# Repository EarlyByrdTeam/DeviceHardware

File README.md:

# DeviceHardware
EAGLE CAD files for EB device

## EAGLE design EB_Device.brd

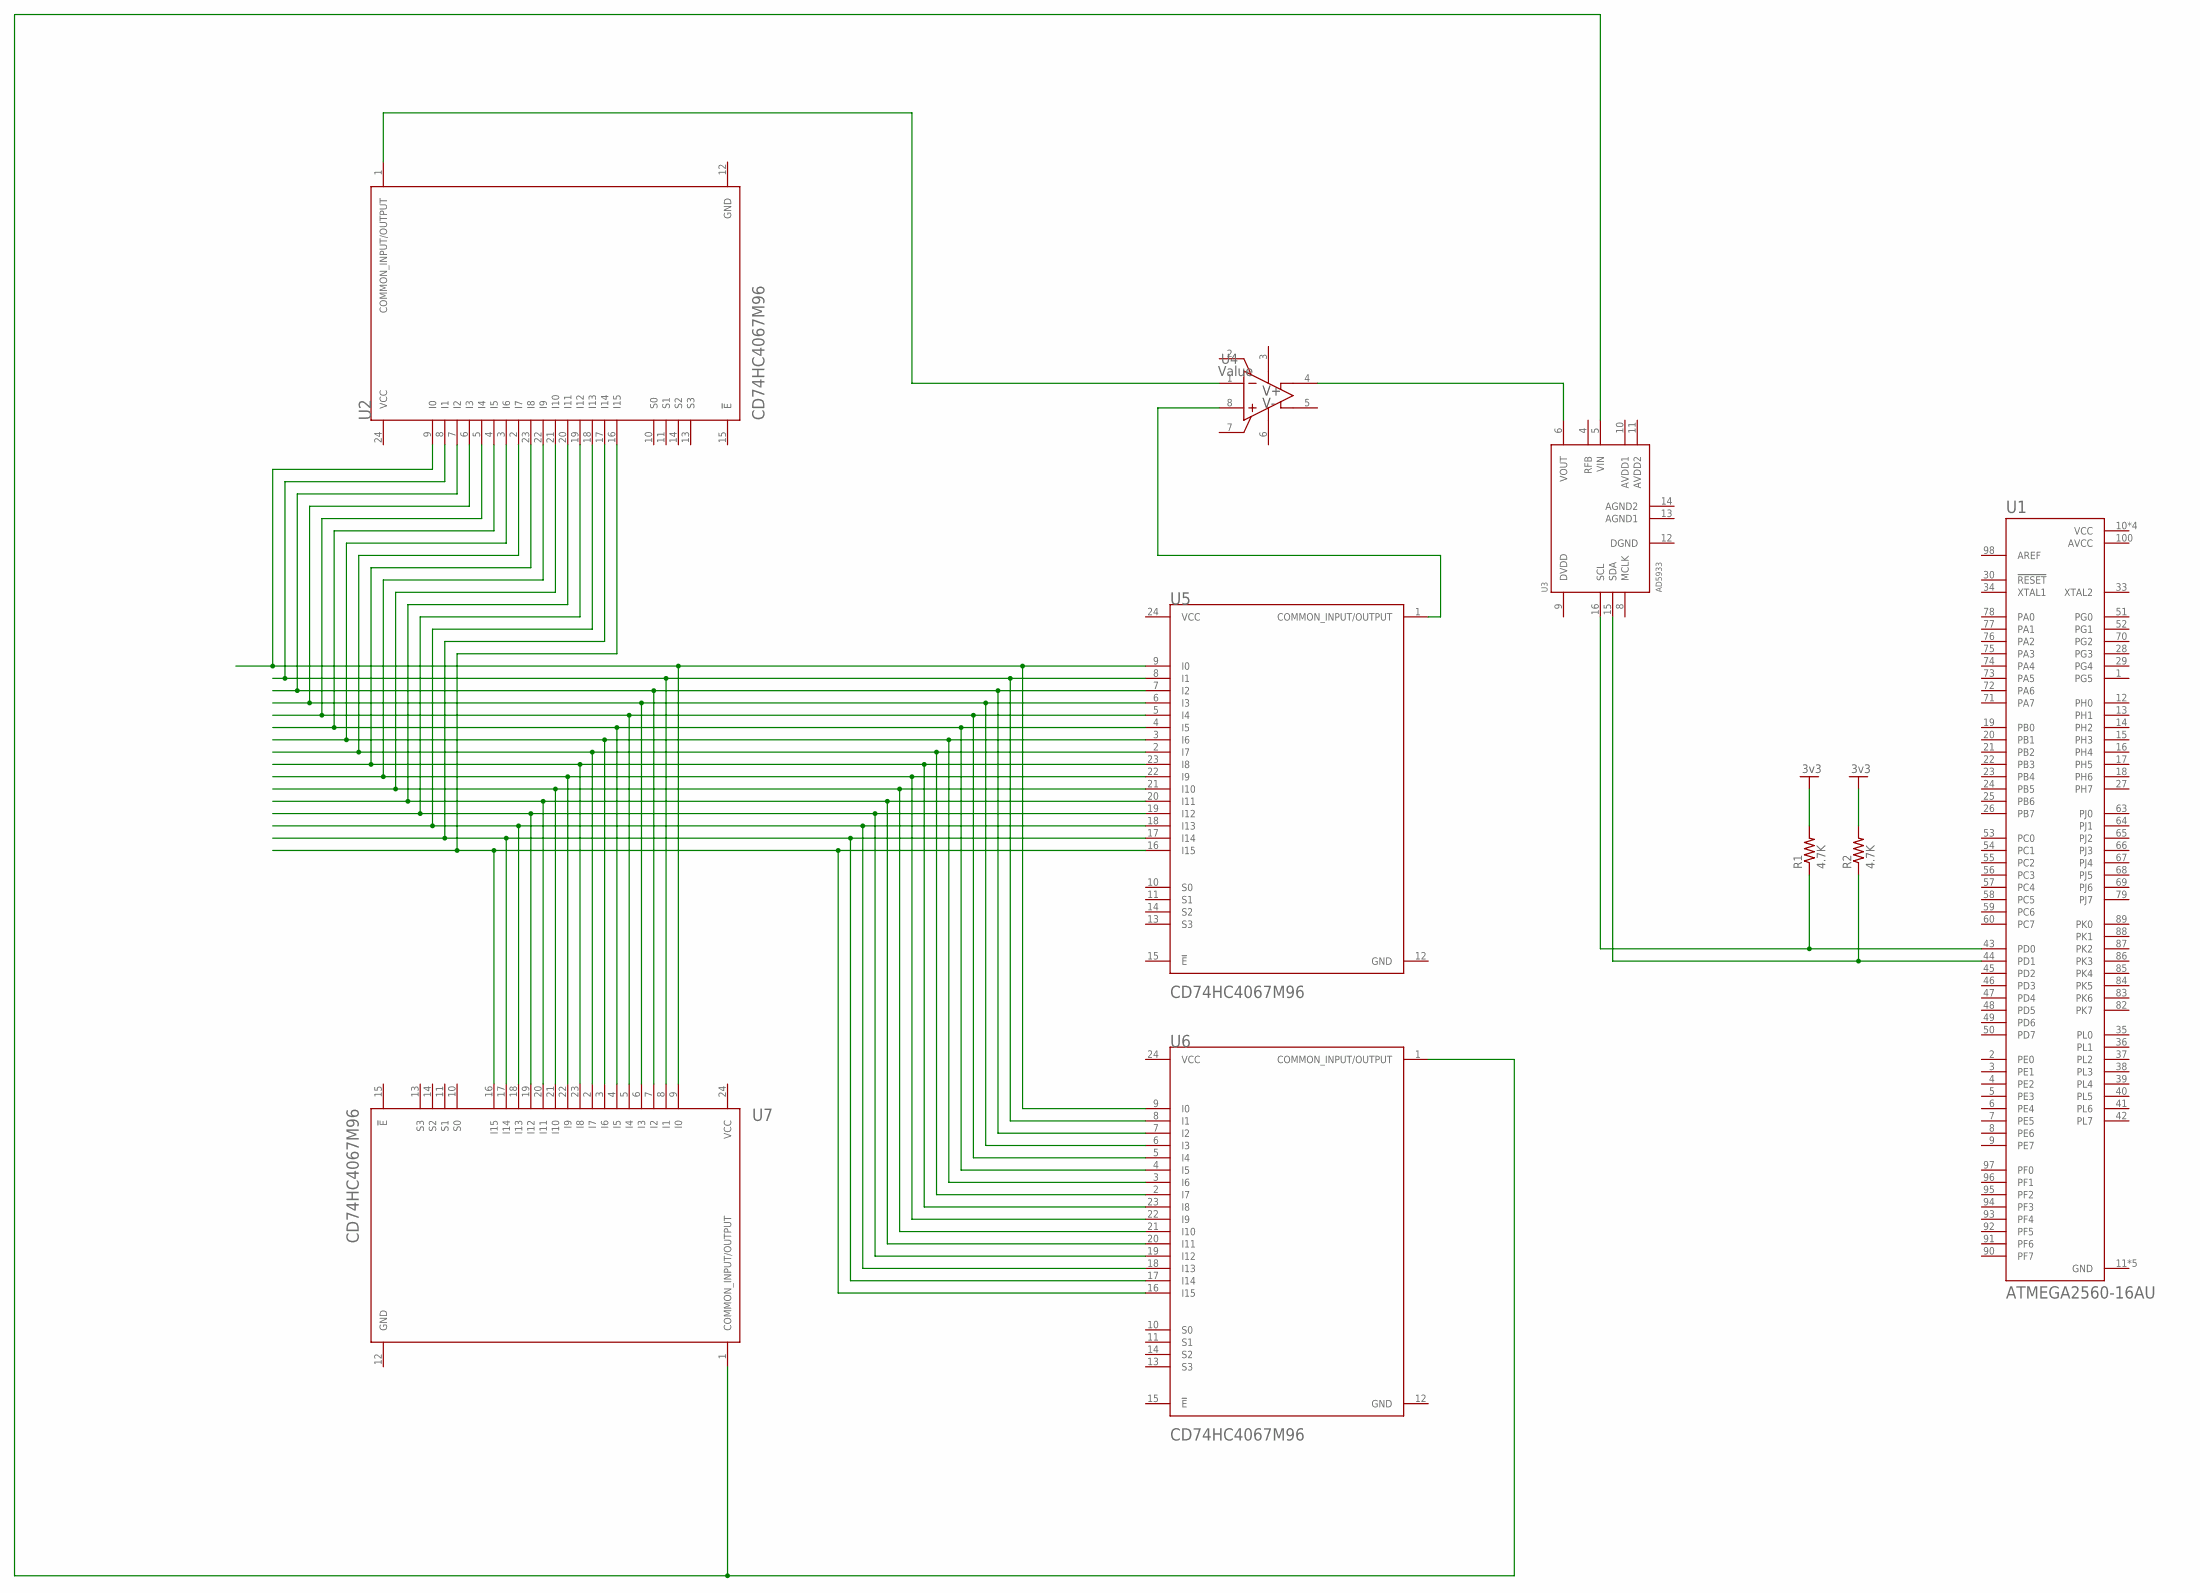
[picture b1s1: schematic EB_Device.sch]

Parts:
R1, R2: 4.7K; 0204V
U1: ATMEGA2560-16AU; QFP50P1600X1600X120-100N
U2, U5, U6, U7: TEXAS_INSTRUMENTS_CD74HC4067M96TEXAS_INSTRUMENTS_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; TEXAS_INSTRUMENTS_CD74HC4067M96_0
U3: AD5933; SSOP16
U4: Value; DGK0008A_N

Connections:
AVCC: U1.100 (AVCC)
GND: R1.2, R2.2, U1.11 (GND), U1.32 (GND), U1.62 (GND), U1.81 (GND), U1.99 (GND), U2.12 (GND), U5.12 (GND), U6.12 (GND), U7.12 (GND)
unnamed: U2.9 (I0), U5.9 (I0), U6.9 (I0), U7.9 (I0)
unnamed: U2.2 (I7), U2.3 (I6), U2.4 (I5), U2.5 (I4), U2.6 (I3), U2.7 (I2), U2.8 (I1), U2.16 (I15), U2.17 (I14), U2.18 (I13), U2.19 (I12), U2.20 (I11), U2.21 (I10), U2.22 (I9), U2.23 (I8), U5.2 (I7), U5.3 (I6), U5.4 (I5), U5.5 (I4), U5.6 (I3), U5.7 (I2), U5.8 (I1), U5.16 (I15), U5.17 (I14), U5.18 (I13), U5.19 (I12), U5.20 (I11), U5.21 (I10), U5.22 (I9), U5.23 (I8), U6.2 (I7), U6.3 (I6), U6.4 (I5), U6.5 (I4), U6.6 (I3), U6.7 (I2), U6.8 (I1), U6.16 (I15), U6.17 (I14), U6.18 (I13), U6.19 (I12), U6.20 (I11), U6.21 (I10), U6.22 (I9), U6.23 (I8), U7.2 (I7), U7.3 (I6), U7.4 (I5), U7.5 (I4), U7.6 (I3), U7.7 (I2), U7.8 (I1), U7.16 (I15), U7.17 (I14), U7.18 (I13), U7.19 (I12), U7.20 (I11), U7.21 (I10), U7.22 (I9), U7.23 (I8)
unnamed: U2.1 (COMMON_INPUT/OUTPUT), U4.1 (VIN-)
unnamed: U4.8 (VIN+), U5.1 (COMMON_INPUT/OUTPUT)
unnamed: U3.6 (VOUT), U4.4 (VOUT+)
unnamed: U3.5 (VIN), U6.1 (COMMON_INPUT/OUTPUT), U7.1 (COMMON_INPUT/OUTPUT)
unnamed: R2.1, U1.44 (PD1), U3.15 (SDA)
unnamed: R1.1, U1.43 (PD0), U3.16 (SCL)
VCC: U1.10 (VCC), U1.31 (VCC), U1.61 (VCC), U1.80 (VCC), U2.24 (VCC), U5.24 (VCC), U6.24 (VCC), U7.24 (VCC)
VS+: U4.3 (VS+)
VS-: U4.6 (VS-)

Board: 2 copper layers, 9 parts (0 on the bottom side), 10 nets, no tracks yet.

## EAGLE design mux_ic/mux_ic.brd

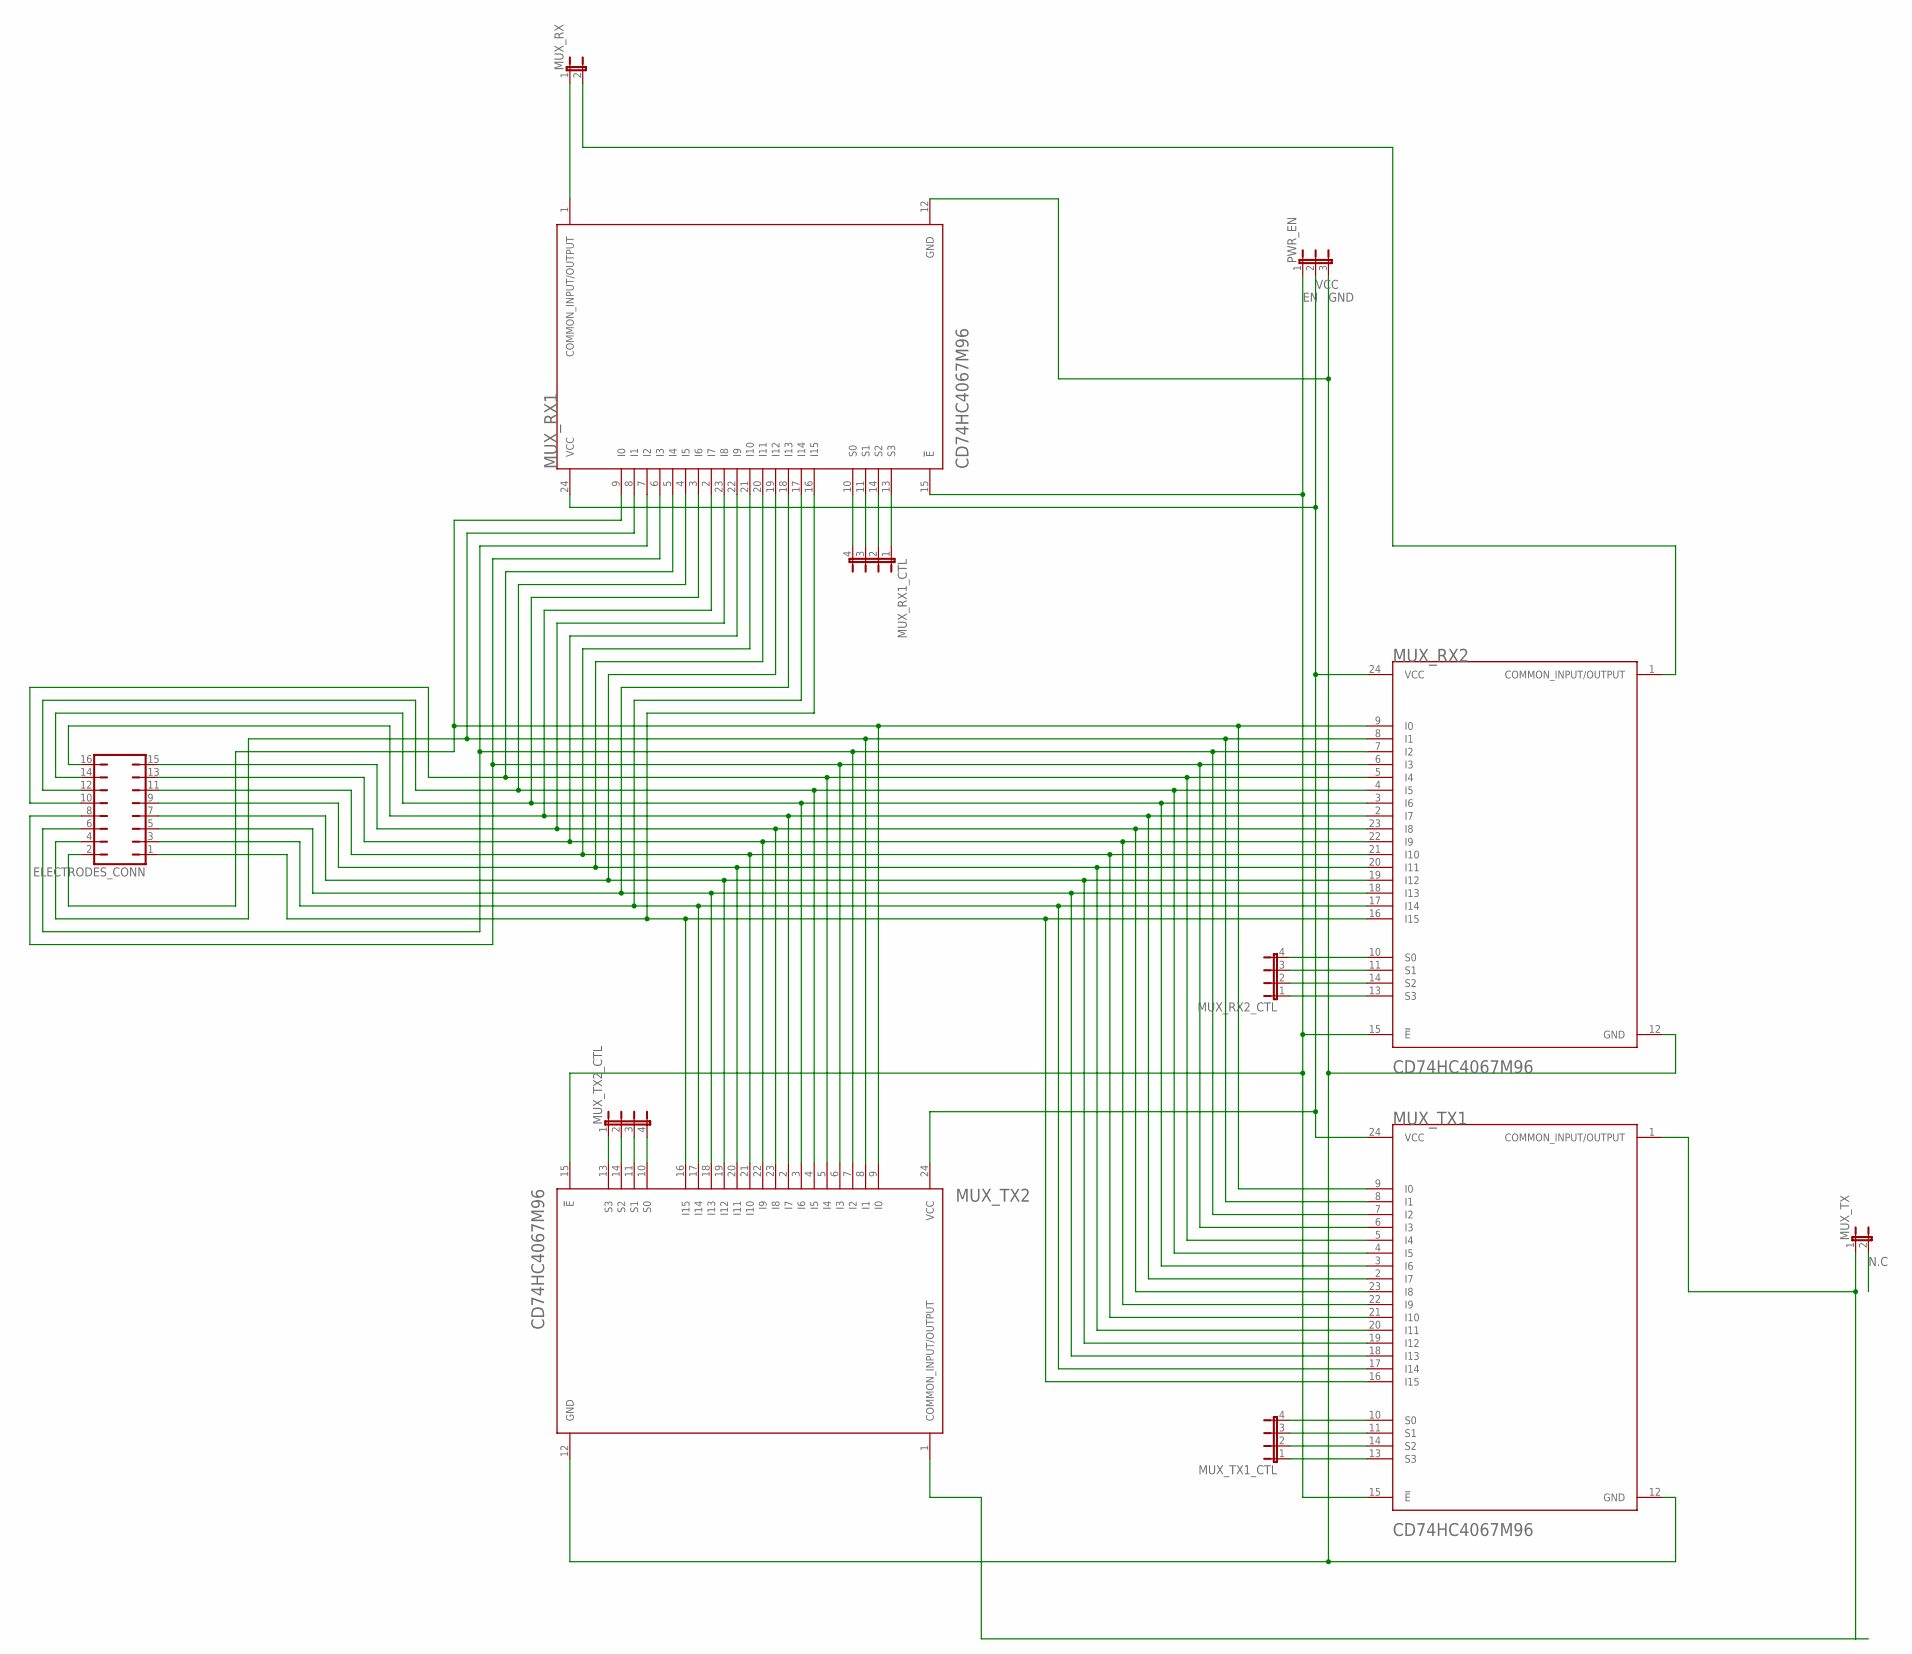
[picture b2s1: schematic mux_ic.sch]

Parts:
ELECTRODES_CONN: JP8Q
MUX_RX: JP1E; JP1
MUX_RX1, MUX_RX2: TEXAS_INSTRUMENTS_CD74HC4067M96TEXAS_INSTRUMENTS_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; TEXAS_INSTRUMENTS_CD74HC4067M96_0
MUX_RX1_CTL, MUX_RX2_CTL: JP4E; JP4
MUX_TX: JP1E; JP1
MUX_TX1, MUX_TX2: TEXAS_INSTRUMENTS_CD74HC4067M96TEXAS_INSTRUMENTS_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; TEXAS_INSTRUMENTS_CD74HC4067M96_0
MUX_TX1_CTL, MUX_TX2_CTL: JP4E; JP4
PWR_EN: JP2W

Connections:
EN: MUX_RX1.15 (!E!), MUX_RX2.15 (!E!), MUX_TX1.15 (!E!), MUX_TX2.15 (!E!), PWR_EN.1
GND: MUX_RX1.12 (GND), MUX_RX2.12 (GND), MUX_TX1.12 (GND), MUX_TX2.12 (GND), PWR_EN.3
unnamed: ELECTRODES_CONN.2, MUX_RX1.9 (I0), MUX_RX2.9 (I0), MUX_TX1.9 (I0), MUX_TX2.9 (I0)
unnamed: ELECTRODES_CONN.1, ELECTRODES_CONN.3, ELECTRODES_CONN.4, ELECTRODES_CONN.5, ELECTRODES_CONN.6, ELECTRODES_CONN.7, ELECTRODES_CONN.8, ELECTRODES_CONN.9, ELECTRODES_CONN.10, ELECTRODES_CONN.12, ELECTRODES_CONN.13, ELECTRODES_CONN.14, ELECTRODES_CONN.15, ELECTRODES_CONN.16, MUX_RX1.2 (I7), MUX_RX1.3 (I6), MUX_RX1.4 (I5), MUX_RX1.5 (I4), MUX_RX1.6 (I3), MUX_RX1.7 (I2), MUX_RX1.8 (I1), MUX_RX1.16 (I15), MUX_RX1.17 (I14), MUX_RX1.18 (I13), MUX_RX1.19 (I12), MUX_RX1.20 (I11), MUX_RX1.22 (I9), MUX_RX1.23 (I8), MUX_RX2.2 (I7), MUX_RX2.3 (I6), MUX_RX2.4 (I5), MUX_RX2.5 (I4), MUX_RX2.6 (I3), MUX_RX2.7 (I2), MUX_RX2.8 (I1), MUX_RX2.16 (I15), MUX_RX2.17 (I14), MUX_RX2.18 (I13), MUX_RX2.19 (I12), MUX_RX2.20 (I11), MUX_RX2.22 (I9), MUX_RX2.23 (I8), MUX_TX1.2 (I7), MUX_TX1.3 (I6), MUX_TX1.4 (I5), MUX_TX1.5 (I4), MUX_TX1.6 (I3), MUX_TX1.7 (I2), MUX_TX1.8 (I1), MUX_TX1.16 (I15), MUX_TX1.17 (I14), MUX_TX1.18 (I13), MUX_TX1.19 (I12), MUX_TX1.20 (I11), MUX_TX1.22 (I9), MUX_TX1.23 (I8), MUX_TX2.2 (I7), MUX_TX2.3 (I6), MUX_TX2.4 (I5), MUX_TX2.5 (I4), MUX_TX2.6 (I3), MUX_TX2.7 (I2), MUX_TX2.8 (I1), MUX_TX2.16 (I15), MUX_TX2.17 (I14), MUX_TX2.18 (I13), MUX_TX2.19 (I12), MUX_TX2.20 (I11), MUX_TX2.22 (I9), MUX_TX2.23 (I8)
unnamed: MUX_RX.1, MUX_RX1.1 (COMMON_INPUT/OUTPUT)
unnamed: MUX_RX.2, MUX_RX2.1 (COMMON_INPUT/OUTPUT)
unnamed: MUX_TX.1, MUX_TX1.1 (COMMON_INPUT/OUTPUT), MUX_TX2.1 (COMMON_INPUT/OUTPUT)
unnamed: ELECTRODES_CONN.11, MUX_RX1.21 (I10), MUX_RX2.21 (I10), MUX_TX1.21 (I10), MUX_TX2.21 (I10)
unnamed: MUX_TX1.10 (S0), MUX_TX1_CTL.4
unnamed: MUX_TX1.11 (S1), MUX_TX1_CTL.3
unnamed: MUX_TX1.14 (S2), MUX_TX1_CTL.2
unnamed: MUX_TX1.13 (S3), MUX_TX1_CTL.1
unnamed: MUX_TX2.13 (S3), MUX_TX2_CTL.1
unnamed: MUX_TX2.14 (S2), MUX_TX2_CTL.2
unnamed: MUX_TX2.11 (S1), MUX_TX2_CTL.3
unnamed: MUX_TX2.10 (S0), MUX_TX2_CTL.4
unnamed: MUX_RX2.10 (S0), MUX_RX2_CTL.4
unnamed: MUX_RX2.11 (S1), MUX_RX2_CTL.3
unnamed: MUX_RX2.14 (S2), MUX_RX2_CTL.2
unnamed: MUX_RX2.13 (S3), MUX_RX2_CTL.1
unnamed: MUX_RX1.10 (S0), MUX_RX1_CTL.4
unnamed: MUX_RX1.11 (S1), MUX_RX1_CTL.3
unnamed: MUX_RX1.14 (S2), MUX_RX1_CTL.2
unnamed: MUX_RX1.13 (S3), MUX_RX1_CTL.1
N.C: MUX_TX.2
VCC: MUX_RX1.24 (VCC), MUX_RX2.24 (VCC), MUX_TX1.24 (VCC), MUX_TX2.24 (VCC), PWR_EN.2

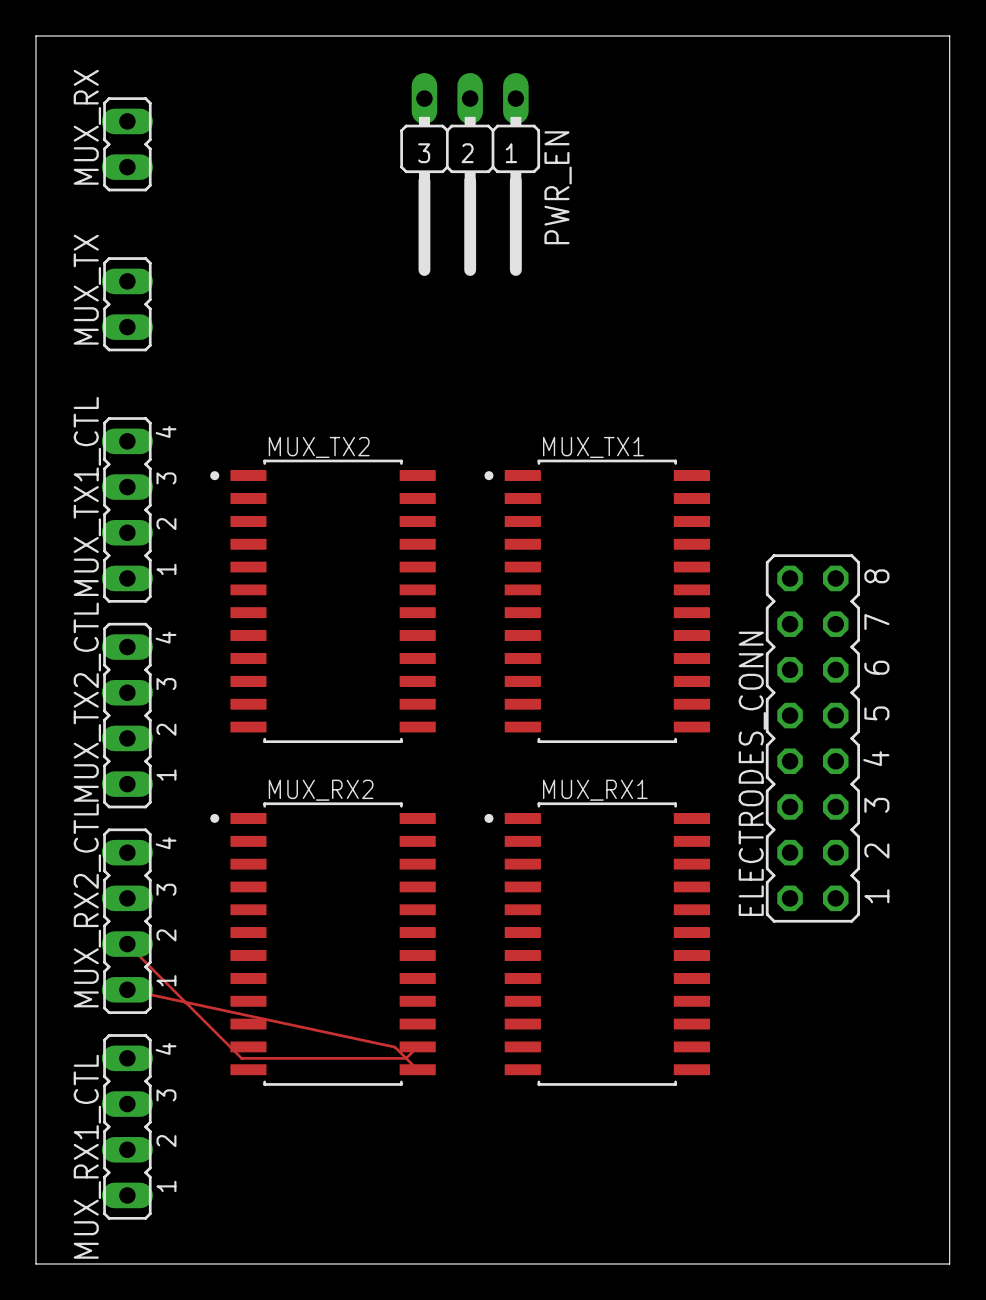
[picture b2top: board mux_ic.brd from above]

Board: 2 copper layers, 50.8 x 68.2 mm, 12 parts (0 on the bottom side), 25 nets.

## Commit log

2021-01-10 finished schematic, started on pcb
2021-01-10 reorganizing
2021-01-12 update to receive and send
2021-01-14 Gentrified board layout and component names
2021-02-06 Routed EarlyByrd board
2021-02-21 Add files via upload
    Bill of Materials for MUX board
2021-03-02 Gerber Files
2021-05-15 Renamed nets
